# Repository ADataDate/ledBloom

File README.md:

# Desert Bloom WS2812B Addressable LED for wearables

## Features
* Rounded Edges so they don't snag on clothing
* Teeny tiny but with 4 holes large enough to mount them on things using thread, safety pins, etc
* Clearly labeled connection points on front and back
* built in decoupling cap
* 0.1" headers to use with any 0.1" connector which is very common. 
* Does not use SMD pads which tend to lift and ruin an LED

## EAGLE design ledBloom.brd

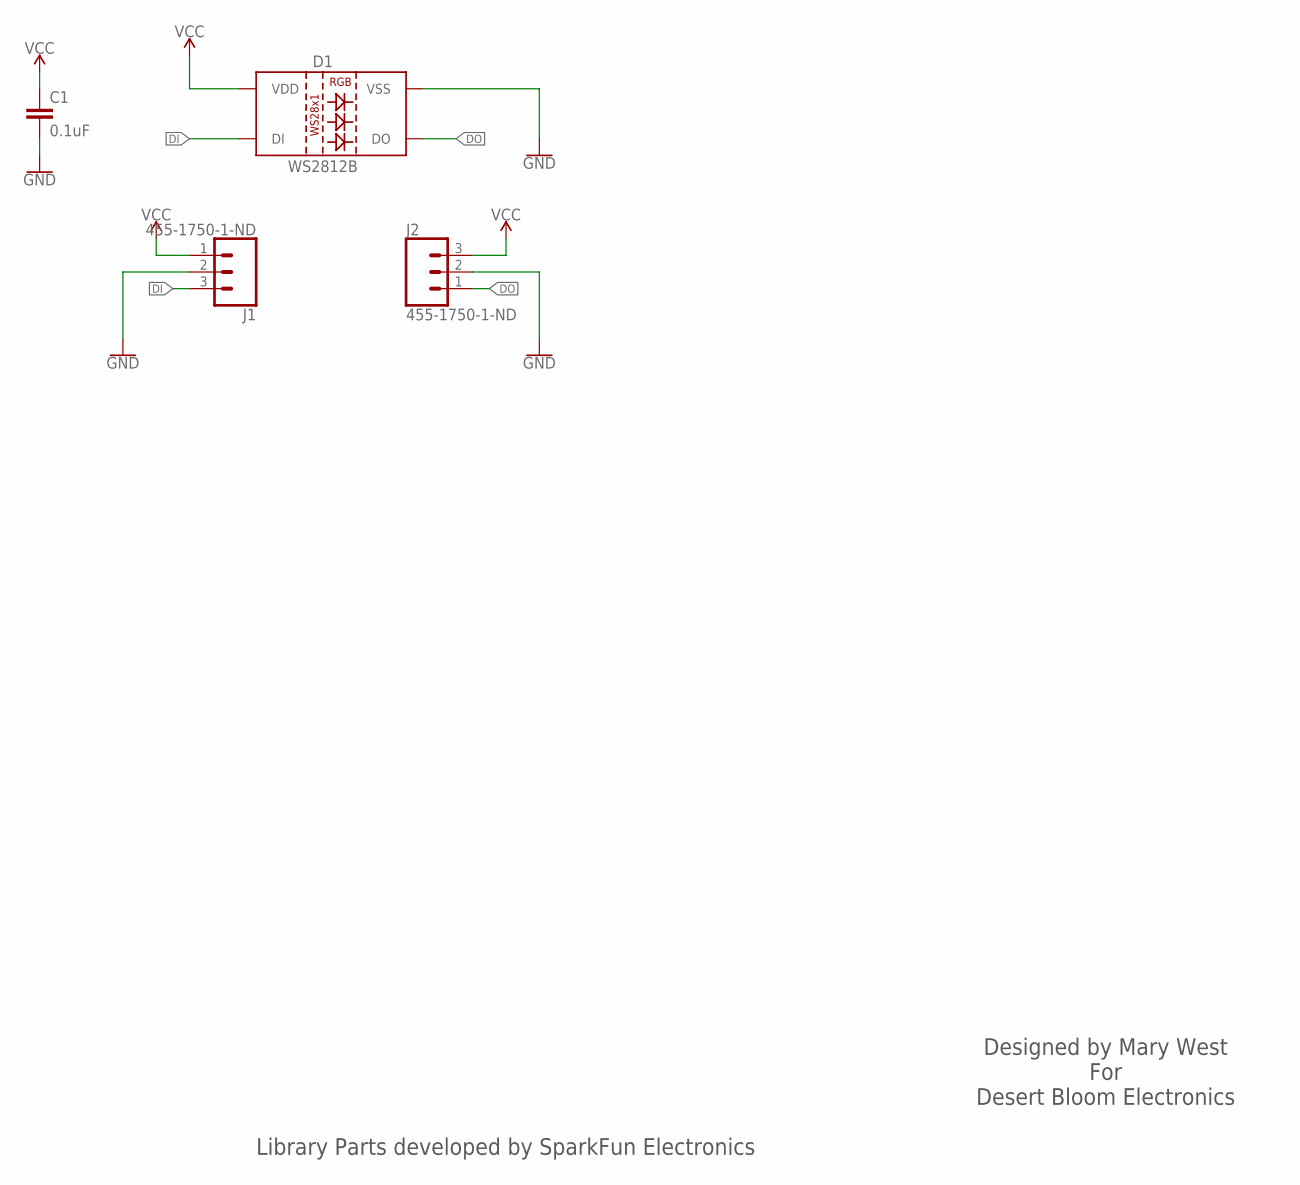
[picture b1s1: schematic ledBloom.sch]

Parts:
C1: 0.1uF; 0603
D1: WS2812B
J1, J2: 455-1750-1-ND; 1X03

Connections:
DI: D1.4 (DI), J1.3
DO: D1.2 (DO), J2.1
GND: C1.2, D1.3 (VSS), J1.2, J2.2
VCC: C1.1, D1.1 (VDD), J1.1, J2.3

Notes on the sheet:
Designed by Mary West For Desert Bloom Electronics
Library Parts developed by SparkFun Electronics

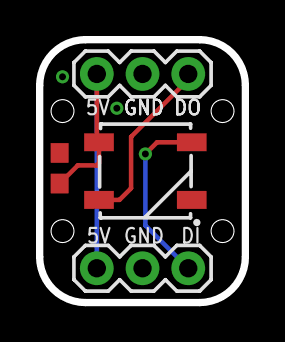
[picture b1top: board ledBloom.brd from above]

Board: 2 copper layers, 11.4 x 14.6 mm, 4 parts (0 on the bottom side), 4 nets.

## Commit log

2018-02-26 updating README
2018-03-21 adding production files
2018-03-21 Updating Silk, adding Desert Bloom to Sch

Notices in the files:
parts and their libraries:
SparkFun-Capacitors: Licensing: Creative Commons ShareAlike 4.0 International - https://creativecommons.org/licenses/by-sa/4.0
